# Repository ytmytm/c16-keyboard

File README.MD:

# C16 USB Keyboard

This project is designed to allow a modern USB keyboard to be used with a Commodore C16 or Commodore C64 instead of the original Commodore keyboard.

It is intended to be plugged into the internal 20-pin keyboard connector.

This project was forked from the [C128 USB Keyboard project](https://github.com/ytmytm/C128-keyboard),
which was based on [Hartland/C64-Keyboard](https://github.com/Hartland/C64-Keyboard).
The hardware and firmware have been adapted to the C16 keyboard matrix and MT8808 switch chip.

Only the USB interface is retained; PS/2 keyboards are becoming retro themselves.

This project requires a Seeed Studio XIAO SAMD21, which has a USB-C socket. Use a USB-A female to USB-C male OTG adapter to connect a standard PC keyboard.

-- Maciej 'YTM/Elysium' Witkowiak

<!---  -->

# Features

- supports USB HID boot-protocol keyboards, including compatible wireless USB receivers
- C16 positional and symbolic maps switchable on the fly
- OLED display support
- adapter can be plugged directly into keyboard port

# PCB and schematic

Use KiCad to open the project in [kicad-c128keyb](kicad-c128keyb/) folder.

In the [kicad-c128keyb/plots](kicad-c128keyb/plots) you will find ready to use Gerber files for manufacturing
as well as [schematic](kicad-c128keyb/plots/kicad-c128keyb.pdf)

Use the Gerber files from this repository when ordering the C16 PCB.

## Parts

* SEEED XIAO SAMD21 (important: SAMD21, not RP2040)
* U1: MT8808
* U2: 74HCT595
* C1, C2: 100n capacitors
* pin headers and sockets
* 128x32 SSD1306 I2C OLED display (optional)

C16 option:

* use J5 as keyboard connector
* J4 to provide power, connect +5V to the square pad
* don't install Q1 and R1

C64 option:

* use J2 as keyboard connector
* Q1: 2N3904 transistors (or any other NPN, like S9013)
* R1: 10K resistors

### C16 option

There is no +5V pin connected to keyboard connector in C16. Connect +5V from anywhere inside computer (e.g. one of the legs of C22 - yellow square on the photo below) to the square pad of J4.

### Restore key (C64 only)

Install Q1 and R1.

# Firmware

The sketch is in [SEEED/C16_keyboard](SEEED/C16_keyboard/). Keep all files in
that folder together when copying it to another computer.

## Install and upload with Arduino IDE

1. Install the **Seeed SAMD Boards** package and select the **Seeeduino XIAO**
   board (SAMD21). Follow the [Seeed setup instructions](https://wiki.seeedstudio.com/Seeeduino-XIAO/#software)
   to add the board package URL if necessary.
2. Use the Library Manager to install **[U8g2](https://github.com/olikraus/U8g2_Arduino)**
   and **[ShiftRegister74HC595](https://github.com/Simsso/ShiftRegister74HC595)**.
   U8g2 is required to compile the sketch even when no OLED is connected.
3. Download **`SEEED/C64_USB_Host_Library_SAMD.zip` from this repository**
   ([download the matching ZIP](SEEED/C64_USB_Host_Library_SAMD.zip)). In the IDE,
   choose **Sketch > Include Library > Add .ZIP Library** and select that local
   file. Alternatively, replace the installed library with this checkout's
   [source directory](SEEED/C64_USB_Host_Library_SAMD).
   A generic USB host library is not a substitute for this modified version.
4. Open [C16_keyboard.ino](SEEED/C16_keyboard/C16_keyboard.ino) in the Arduino IDE.
5. Disconnect the USB keyboard/OTG adapter and connect the XIAO's USB-C port
   to the computer with a USB data cable. Select the board's port and upload.
   If the port is missing or upload fails, enter the bootloader as described
   below, select its port, and try again.
6. Disconnect the programming cable, reconnect the keyboard through the OTG
   adapter, and power the adapter using the configuration described above.

Install the matching USB library on **the computer that compiles the sketch**.
Updating only the sketch or the Git checkout does not update an independently
installed library. The sketch rejects older library headers at compile time.

### Replacing the library on Windows

1. Close Arduino IDE and locate the sketchbook folder shown in its Preferences.
   Its library directory is usually `Documents\Arduino\libraries`, but the
   sketchbook may be elsewhere, including under OneDrive.
2. Move the old `C64_USB_Host_Library_SAMD` folder outside the `libraries`
   directory, then extract the current ZIP there. Replace the whole folder.
3. Check that the resulting layout is
   `libraries\C64_USB_Host_Library_SAMD\library.properties`, with no extra
   nested `C64_USB_Host_Library_SAMD` directory.
4. Restart the IDE and compile again. If multiple libraries are reported for
   `KeyboardController.h`, enable verbose compilation output and check the
   selected path. Remove or replace any outdated copy being selected.

On systems that support symbolic links, the installed library directory can
instead link to this checkout's `SEEED/C64_USB_Host_Library_SAMD` directory.
Move the old copy outside `libraries` and restart the IDE after changing it.

## Compile with the checkout's library using Arduino CLI

Run from the repository root. The Seeed SAMD board package, U8g2 and
ShiftRegister74HC595 must already be installed for Arduino CLI.

Bash (Linux/macOS):

```sh
arduino-cli compile \
  --fqbn Seeeduino:samd:seeed_XIAO_m0 \
  --library "$PWD/SEEED/C64_USB_Host_Library_SAMD" \
  SEEED/C16_keyboard
```

PowerShell (Windows):

```powershell
arduino-cli compile --fqbn Seeeduino:samd:seeed_XIAO_m0 --library ".\SEEED\C64_USB_Host_Library_SAMD" ".\SEEED\C16_keyboard"
```

The explicit [`--library` option](https://arduino.github.io/arduino-cli/1.5/sketch-build-process/#dependency-resolution)
has priority over libraries installed in the sketchbook. These commands use
the source directory directly, so no USB library ZIP installation is needed.
They compile the firmware; use the Arduino IDE or an appropriate CLI upload
command to upload it to the board.

The automated build pins Arduino CLI **1.5.1**, Seeed SAMD Boards **1.8.6**,
U8g2 **2.36.19** and ShiftRegister74HC595 **1.3.1**; see
[firmware.yml](.github/workflows/firmware.yml) for the build configuration.

## Entering the bootloader (double reset)

The original XIAO SAMD21 has reset pads rather than an onboard reset button.
To enter its bootloader:

1. Disconnect the keyboard/OTG adapter and connect the XIAO to the computer
   with a USB data cable.
2. Briefly bridge the two **RST reset pads twice in quick succession**, removing
   the bridge between the two touches. See [Seeed's reset-pad illustration](https://wiki.seeedstudio.com/Seeeduino-XIAO/#enter-bootloader-mode)
   for the pad locations. If your board has a reset button, press it twice.
3. The bootloader LED should pulse. With a UF2-enabled bootloader, a removable
   drive normally named **Arduino** appears, containing `INFO_UF2.TXT`.
   A bootloader serial port may also appear; on Windows its COM number may
   differ from the application port. Select that port for an IDE upload.

A single reset restarts the application. **Print Screen on the USB keyboard
only resets the adapter's keys and settings; it does not enter the bootloader.**

## Uploading a UF2 file by copying it to the boot drive

The [XIAO SAMD21 UF2 bootloader supports drag-and-drop flashing](https://wiki.seeedstudio.com/Seeeduino-XIAO-CircuitPython/#installing-circuitpython).
With a UF2-enabled bootloader and a UF2 build of **this project's firmware for
XIAO SAMD21**, no Arduino IDE is needed on the computer doing the upload:

1. Enter the bootloader using the double-reset procedure above.
2. Copy the firmware `.uf2` file to the **Arduino** removable drive using
   Windows File Explorer or your system's file manager.
3. Wait for copying to finish. The board normally restarts automatically and
   the boot drive disappears. Reconnect the keyboard/OTG adapter for use.

Prebuilt firmware is produced by the [Firmware build workflow](.github/workflows/firmware.yml)
and can be downloaded from a successful Actions run or a GitHub Release after
its build completes. The UF2 already contains the compiled libraries; its
recipient does not need Arduino IDE or the USB library ZIP.

Compiled binaries are not tracked in Git. The library ZIP is installed on the
build computer; it is not copied to the board's boot drive.
A `.bin` file cannot be used by simply renaming it to `.uf2`.

### Creating a UF2 from an Arduino build

1. Build for **Seeeduino XIAO (SAMD21)** with the matching USB library, then
   use **Sketch > Export Compiled Binary** in the Arduino IDE. Locate the
   application binary, normally named `C16_keyboard.ino.bin`.
2. Download [uf2conv.py](https://github.com/microsoft/uf2/blob/master/utils/uf2conv.py)
   and [uf2families.json](https://github.com/microsoft/uf2/blob/master/utils/uf2families.json)
   from Microsoft's UF2 project and place them alongside the binary.
3. In that directory, run the conversion with Python 3 (adjust the binary
   filename if your build uses a different one):

   ```sh
   python uf2conv.py --convert --family SAMD21 --base 0x2000 --output C16_keyboard.uf2 C16_keyboard.ino.bin
   ```

Use the application binary from this sketch's XIAO SAMD21 build, without a
bootloader image prepended. The `0x2000` application address matches the
[Seeed XIAO linker configuration](https://github.com/Seeed-Studio/ArduinoCore-samd/blob/master/variants/XIAO_m0/linker_scripts/gcc/flash_with_bootloader.ld).
The conversion only creates the UF2 file; copy it to the boot drive separately.

## OLED and firmware version

The optional display is a **128 × 32 SSD1306 I²C OLED at address `0x3C`**.
The firmware probes for it at startup and skips display operations if it does
not respond. The keyboard functions work without it.

The OLED shows the firmware release date below startup USB status messages,
for example `USB Configuring` / `FW 2026-10-31`. The version also appears below
`USB Running`. Status messages are cleared after about five seconds of
inactivity; key events replace them with the key display.

Set the release date in [firmware_version.h](SEEED/C16_keyboard/firmware_version.h)
when preparing a new firmware release. Recompiling the same source does not
change its version.

## Keyboard compatibility

The USB driver uses HID boot-protocol reports with six ordinary key slots and
separate modifier bits. A keyboard that only supports a proprietary or
NKRO-only report format may not work. Wireless keyboards need a compatible
USB receiver; Bluetooth-only keyboards cannot connect directly.

The adapter reads raw USB HID usages, so the PC's operating-system keyboard
layout does not configure it. The symbolic maps assume US-style key labels.
For troubleshooting, Right Shift should appear as HID usage `0xE5` with
modifier mask `0x20`. `getOemKey()` returns the HID usage; `getKey()` returns
ASCII and is not used to map the Commodore keyboard matrix.

The companion C64 sketch is [SEEED/C64_keyboard/C64_keyboard.ino](SEEED/C64_keyboard/C64_keyboard.ino).
It uses the same modified USB library. Select that folder instead of
`SEEED/C16_keyboard` when building for C64. The C16 firmware has only its
C16 positional and symbolic layouts and no joystick emulation.

## Tests and automated builds

Run the following commands from the repository root with Python 3 and g++ installed:

```sh
python3 tests/test_keyboard_events.py
python3 tests/test_keyboard_events.py C64
python3 -m unittest discover -s tests -p 'test_firmware_artifacts.py' -v
```

The tests exercise the real HID parser and firmware callbacks with mocked
hardware, including simultaneous modifiers, both Shifts, Shift Lock,
differential Shift, shared switches, saved releases, reset and USB reconnect.
See [tests/README.md](tests/README.md).

GitHub Actions runs these tests, compiles both sketches and packages verified
C16 `.bin`, `.elf` and `.uf2` files, build metadata and SHA-256 checksums.
A published release also receives those files. Before publishing, update
`SEEED/C16_keyboard/firmware_version.h`, run the tests and build, commit the
changes and tag that commit `vYYYY-MM-DD` to match the firmware date. Push the
commit and tag, then publish a GitHub Release for that tag to trigger attachment
of the verified firmware files. A tag push alone does not attach release files.
If changing the USB library, rebuild its installation ZIP with
`python3 tools/package_usb_library.py` and commit the updated ZIP too.

# Keyboard mapping

Key maps are defined in [SEEED/C16_keyboard/keymaps.h](SEEED/C16_keyboard/keymaps.h) and [SEEED/C64_keyboard/keymaps.h](SEEED/C64_keyboard/keymaps.h).

You can modify existing ones or add your own.

If you add a new keymap you need to add it to `keymaps[]` array at the bottom of that file. The first key map in that array is the default one.

Press **Pause** to cycle between the two layouts for the selected sketch.
Startup and **Print Screen** reset select the positional layout.
**Scroll Lock** toggles Shift Lock. These settings are not saved across power cycles.

Both physical Shifts, Shift Lock and differential mappings share the C16 Shift
switch. Releases use the mapping saved on key-down, even after a layout change.
Unplugging the USB keyboard clears held keys and Shift Lock.
In the C16 sketch, **Print Screen** clears ordinary held keys and Shift Lock,
selects the positional layout, and restores still-held USB modifiers using that
layout. Release and press an ordinary key again to reactivate it after reset.

The C16 event state uses a fixed table for six ordinary keys and eight modifiers.
The sketch stores its keyboard object statically and prints OLED text directly,
without `std::map`, `new` or Arduino `String` allocations in its own event and
display code.

## C16 positional (default for C16)

This is a mixture of C16/Plus4/C64 and Vice layout.

| USB key | C16 key |
|---------|----------|
| ESC | RUN/STOP |
| F1 | F1 |
| F2 | F4 (shift+F1) |
| F3 | F2 |
| F4 | F5 (shift+F2) |
| F5 | F3 |
| F6 | F6 (shift+F3) |
| F7 | HELP |
| F8 | F7 (shift+HELP) |
| ` ~ | ESC |
| - | + |
| + | - |
| [ | @ |
| ] | * |
| \ | = |
| ; | : |
| ' " | ; |
| Tab | CTRL |
| Caps lock | RUN/STOP |
| Home | CLR/HOME |
| End | RUN/STOP |
| Delete | DEL |
| Backspace | DEL |
| Insert | POUND |
| Page down | Shift+= (left arrow); ignored with Shift |
| Page up | Shift+0 (up arrow); ignored with Shift |
| left CTRL | C= key |
| left/right SHIFT | SHIFT |
| left Windows | ignored |
| right Alt | POUND |
| right Windows | POUND |
| right CTRL | = |
| Print Screen | reset MT8808 switchboard |
| Scroll Lock | Shift Lock |
| Pause | switch to next keymap |
| (keypad) | digits 1-9,0 |
| (cursors) | cursors |

## C16 symbolic

Both physical Shifts map to C16 SHIFT; both Windows keys map to C=.
Right Alt is ignored.

| USB key | C16 key |
|---------|----------|
| ESC | ESC |
| F1 | F1 |
| F2 | F4 (shift+F1) |
| F3 | F2 |
| F4 | F5 (shift+F2) |
| F5 | F3 |
| F6 | F6 (shift+F3) |
| F7 | HELP |
| F8 | F7 (shift+HELP) |
| ` ~ | (left arrow) |
| \ | POUND |
| Tab | CTRL |
| Caps lock | RUN/STOP |
| Home | CLR/HOME |
| End | RUN/STOP |
| Delete | DEL |
| Backspace | DEL |
| left CTRL | CTRL |
| right CTRL | CTRL |
| left Windows | C= key |
| Print Screen | reset MT8808 switchboard |
| Scroll Lock | Shift Lock |
| Pause | switch to next keymap |
| (keypad) | digits 1-9,0 |
| (cursors) | cursors |

As you would expect from standard keycaps, e.g. SHIFT+2 is '@', not '"'.

## C64 positional (default for C64)

This layout works best if you have muscle memory of the original keyboard.

| USB key | C64 key |
|---------|----------|
| ESC | RUN/STOP |
| F1 | F1 |
| F2 | F2 (Shift+F1) |
| F3 | F3 |
| F4 | F4 (Shift+F3) |
| F5 | F5 |
| F6 | F6 (Shift+F5) |
| F7 | F7 |
| F8 | F8 (Shift+F7) |
| F9–F12 | ignored |
| Print Screen | reset MT8808 switchboard |
| Scroll Lock | Shift Lock |
| Pause | switch to next keymap |
| Insert | POUND |
| Home | CLR/HOME |
| Page Up | RESTORE |
| End | RUN/STOP |
| (keypad) | digits 1-9,0 |
| left CTRL | C= key |
| left SHIFT | left SHIFT |
| right SHIFT | right SHIFT |
| AltGr | RESTORE |

## C64 symbolic

As you would expect from standard keycaps, e.g. SHIFT+2 is '@', not '"'.

It uses the same F1–F8 mappings and adapter controls as the C64 positional map.
Other changes:

- Insert maps to INST (Shift+DEL); Delete maps to DEL
- both left and right CTRL mapped to CTRL
- both left and right Windows mapped to C= key
- AltGr is RESTORE

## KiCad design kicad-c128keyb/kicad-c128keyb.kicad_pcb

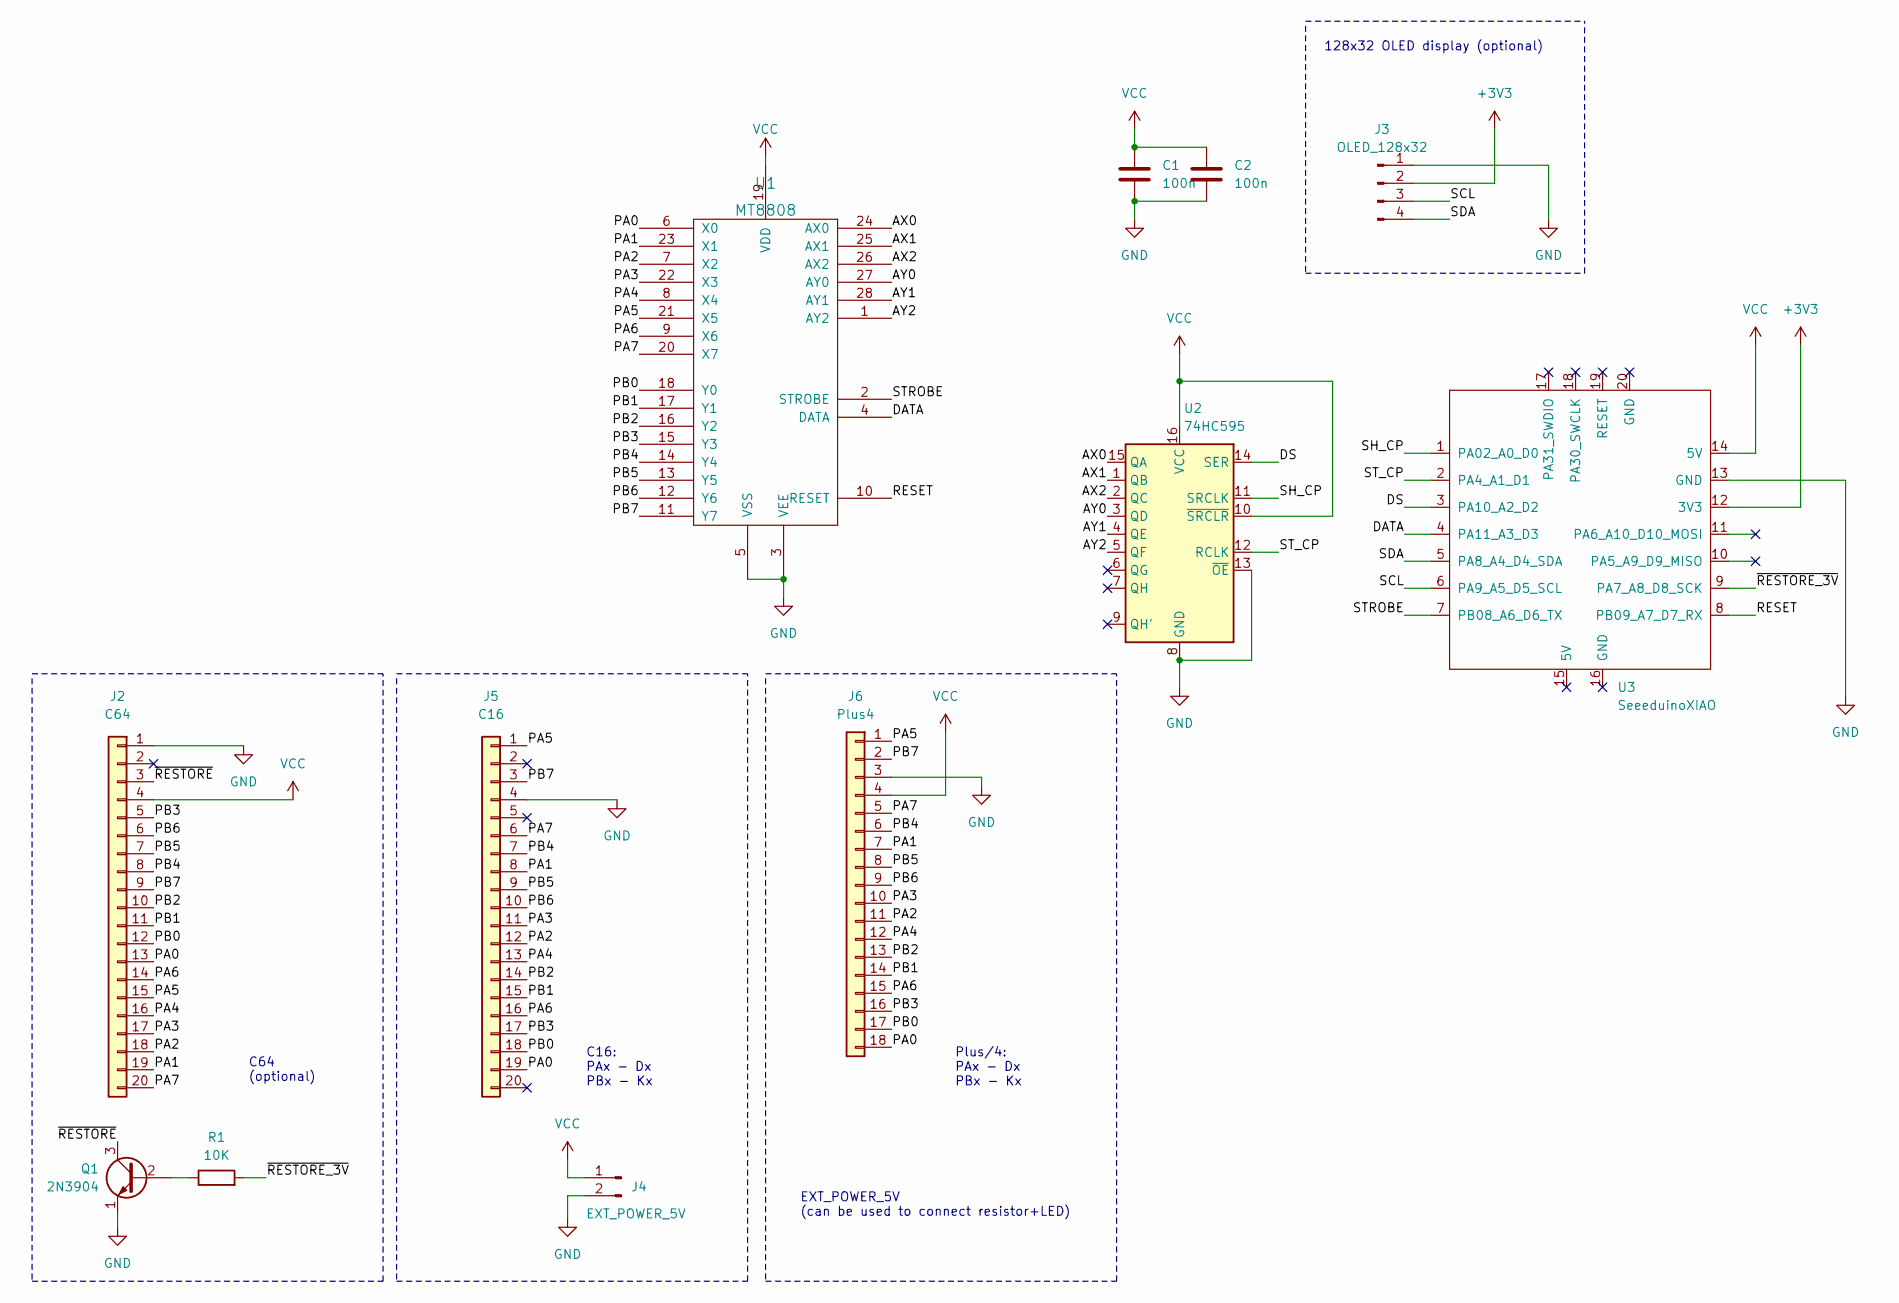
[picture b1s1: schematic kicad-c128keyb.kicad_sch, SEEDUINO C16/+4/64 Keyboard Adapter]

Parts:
C1, C2: 100n; C_Disc_D4.3mm_W1.9mm_P5.00mm
J2: C64; PinHeader_1x20_P2.54mm_Vertical
J3: OLED_128x32; PinHeader_1x04_P2.54mm_Vertical
J4: EXT_POWER_5V; PinHeader_1x02_P2.54mm_Vertical
J5: C16; PinHeader_1x20_P2.54mm_Vertical
J6: Plus4; PLUS4_KEYBOARD
Q1: 2N3904; TO-92_Inline
R1: 10K; R_Axial_DIN0207_L6.3mm_D2.5mm_P7.62mm_Horizontal
U1: MT8808; DIP-28_W15.24mm_Socket
U2: 74HC595; DIP-16_W7.62mm_Socket
U3: SeeeduinoXIAO; XIAO-Generic-Hybrid-14P-2.54-21X17.8MM

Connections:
+3V3: J3.2, U3.12 (3V3)
/AX0: U1.24 (AX0), U2.15 (QA)
/AX1: U1.25 (AX1), U2.1 (QB)
/AX2: U1.26 (AX2), U2.2 (QC)
/AY0: U1.27 (AY0), U2.3 (QD)
/AY1: U1.28 (AY1), U2.4 (QE)
/AY2: U1.1 (AY2), U2.5 (QF)
/DATA: U1.4 (DATA), U3.4 (PA11_A3_D3)
/DS: U2.14 (SER), U3.3 (PA10_A2_D2)
/PA0: J2.13, J5.19, J6.18, U1.6 (X0)
/PA1: J2.19, J5.8, J6.7, U1.23 (X1)
/PA2: J2.18, J5.12, J6.11, U1.7 (X2)
/PA3: J2.17, J5.11, J6.10, U1.22 (X3)
/PA4: J2.16, J5.13, J6.12, U1.8 (X4)
/PA5: J2.15, J5.1, J6.1, U1.21 (X5)
/PA6: J2.14, J5.16, J6.15, U1.9 (X6)
/PA7: J2.20, J5.6, J6.5, U1.20 (X7)
/PB0: J2.12, J5.18, J6.17, U1.18 (Y0)
/PB1: J2.11, J5.15, J6.14, U1.17 (Y1)
/PB2: J2.10, J5.14, J6.13, U1.16 (Y2)
/PB3: J2.5, J5.17, J6.16, U1.15 (Y3)
/PB4: J2.8, J5.7, J6.6, U1.14 (Y4)
/PB5: J2.7, J5.9, J6.8, U1.13 (Y5)
/PB6: J2.6, J5.10, J6.9, U1.12 (Y6)
/PB7: J2.9, J5.3, J6.2, U1.11 (Y7)
/RESET: U1.10 (RESET), U3.8 (PB09_A7_D7_RX)
/SCL: J3.3, U3.6 (PA9_A5_D5_SCL)
/SDA: J3.4, U3.5 (PA8_A4_D4_SDA)
/SH_CP: U2.11 (SRCLK), U3.1 (PA02_A0_D0)
/STROBE: U1.2 (STROBE), U3.7 (PB08_A6_D6_TX)
/ST_CP: U2.12 (RCLK), U3.2 (PA4_A1_D1)
/~RESTORE_3V: R1.2, U3.9 (PA7_A8_D8_SCK)
/~RESTORE: J2.3, Q1.3 (C)
GND: C1.2, C2.2, J2.1, J3.1, J4.2, J5.4, J6.3, Q1.1 (E), U1.3 (VEE), U1.5 (VSS), U2.8 (GND), U2.13 (~OE), U3.13 (GND)
unnamed: Q1.2 (B), R1.1
VCC: C1.1, C2.1, J2.4, J4.1, J6.4, U1.19 (VDD), U2.10 (~SRCLR), U2.16 (VCC), U3.14 (5V)

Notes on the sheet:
C16: PAx - Dx PBx - Kx
C64 (optional)
128x32 OLED display (optional)
EXT_POWER_5V (can be used to connect resistor+LED)
Plus/4: PAx - Dx PBx - Kx

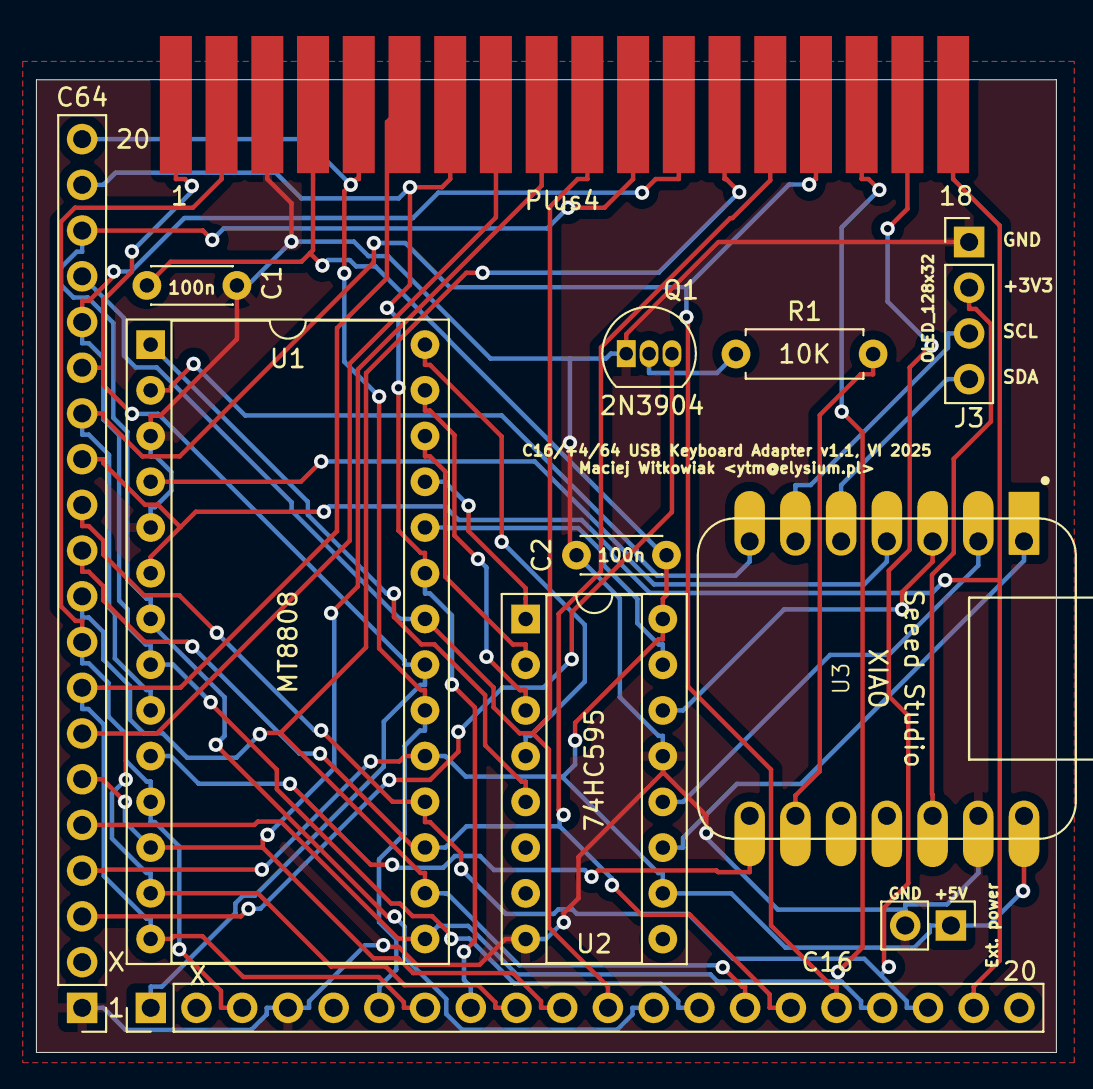
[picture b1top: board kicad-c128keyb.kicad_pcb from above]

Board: 2 copper layers, 56.7 x 54.0 mm, 12 parts (0 on the bottom side), 36 nets.

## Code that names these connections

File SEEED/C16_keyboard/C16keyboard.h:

/*
  C16keyboard - Commodore Keyboard library

  Copyright (c) 2022 Hartland PC LLC
  Written by Robert VanHazinga

  Modified for C16 by Maciej 'YTM/Elysium' Witkowiak


    This program is free software: you can redistribute it and/or modify
    it under the terms of the GNU General Public License as published by
    the Free Software Foundation, either version 3 of the License, or
    (at your option) any later version.

    This program is distributed in the hope that it will be useful,
    but WITHOUT ANY WARRANTY; without even the implied warranty of
    MERCHANTABILITY or FITNESS FOR A PARTICULAR PURPOSE.  See the
    GNU General Public License for more details.

    You should have received a copy of the GNU General Public License
    along with this program.  If not, see <https://www.gnu.org/licenses/>.

*/


#ifndef C16keyboard_h
#define C16keyboard_h

#include <array>

#if defined(ARDUINO) && ARDUINO >= 100
#include "Arduino.h"
#else
#include "WProgram.h"
#endif

//MT88xx control pins
#define ANALOG_SW_DATA      3 // Sets selected cross switch on/off
#define ANALOG_SW_STROBE    6 // Strobe timing pulse
#define ANALOG_SW_RESET     7 // Reset all MT88XX cross switches to off

// I2C DISPLAY
#define SDA_PIN             4 // just for reference, native SEEDUINO XIAO doesn't need these defines
#define SCL_PIN             5

// 74HC595 shift register pins
#define SH_CP_PIN           0 // SRCLK // 11th pin // clock
#define ST_CP_PIN           1 // RCLK  // 12th pin // latch
#define DS_PIN              2 // SER   // 14th pin // data

// Six address bits from the shift register to the MT8808 (8 by 8).
#define ANALOG_SH_AX0     0 // QA (15)
#define ANALOG_SH_AX1     1 // QB (1)
#define ANALOG_SH_AX2     2 // ...
#define ANALOG_SH_AY0     3
#define ANALOG_SH_AY1     4
#define ANALOG_SH_AY2     5
const uint8_t ANALOG_SH_ARRAY[] = { ANALOG_SH_AY2, ANALOG_SH_AY1, ANALOG_SH_AY0, ANALOG_SH_AX2, ANALOG_SH_AX1, ANALOG_SH_AX0 };
// Shift-register outputs QG and QH are unused.

// C16 matrix addresses and adapter actions.
#include "keymapping.h"

class C16KeyInfo {
  public:
    constexpr C16KeyInfo(const uint16_t c, const char* name) :
    m_keycode(c), m_name(name)
    {};
    constexpr auto get_keycode() const { return m_keycode; }
    constexpr const char* get_name() const { return m_name; };
  private:
    const uint16_t m_keycode;
    const char *m_name;
};

// HID boot reports hold at most six ordinary keys and eight modifiers.
struct HeldKey {
    uint8_t usage = 0;
    uint16_t mapped = IGNORE_KEYCODE;
};

class C16keyboard {
  public:
    void begin(void);
    void setKey(uint16_t c, bool kpress, uint8_t kc);
    uint16_t mapkeycode(uint8_t kc);
    void clearAllKeys(void);
    void updateShiftSwitches(void);
    void restoreModifiers(uint8_t modifiers);
    constexpr uint8_t getNumKeyMaps(void);
    const char* getCurrentKeyMapName(void);
};

class C16Key {
  public:
    constexpr C16Key(const int16_t keycode, const uint16_t unshifted, const uint16_t shifted) :
    m_keycode(keycode), m_unshifted(unshifted), m_shifted(shifted)
    {};
    constexpr auto get_keycode() const { return m_keycode; }
    constexpr uint16_t get(bool shifted = false) const {
      return shifted ? m_shifted : m_unshifted;
    }
  private:
    const int16_t m_keycode;
    const uint16_t m_unshifted, m_shifted;
};

using ModifierMap = std::array<uint16_t, 8>;

class C16KeyMap {
  public:
    constexpr C16KeyMap(const char* name, const C16Key *map, const uint16_t mapsize, const ModifierMap &mods) :
    m_name(name), m_map(map), m_mapsize(mapsize), m_mods(mods)
    {};
    constexpr const char* getName() const { return m_name; };
    constexpr const ModifierMap &getMods() const { return m_mods; };
    constexpr C16Key getKey(uint8_t keycode) const {
      for (uint16_t i = 0; i < m_mapsize; ++i) {
        if (m_map[i].get_keycode() == keycode) {
          return m_map[i];
        }
      }
      return C16Key(0, IGNORE_KEYCODE, IGNORE_KEYCODE);
    }
  private:
    const char *m_name;
    const C16Key *m_map;
    const uint16_t m_mapsize;
    const ModifierMap &m_mods;
};

#endif

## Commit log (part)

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2024-10-09 common C16/C64 version for internal mount; despite filenames this is not about C128 anymore; downgraded from MT8816 to MT8808
2024-10-15 move folder to C16
2024-10-15 move files to C16
2024-10-15 docs
2024-10-15 C128->C16 renames
2024-10-16 remove all C128-related, joystick and MT8812/16 stuff
2024-10-16 C16 symbolic keymap and list of key definitions
2024-10-16 correct slash/dot/comma confusion
2024-10-16 reference for key layout definitions
2024-10-16 new PCB render
2024-10-16 drop C128-related files
2024-10-16 C64 firmware
2024-10-16 updated for C16/64 combination
2024-10-22 fix for missed key release events (e.g. in symbolic mapping after shift+' for double-quote, shift had to be released last)
2024-10-22 don't use u8g2 if the display is not connecte (i2c address 0x3c)
2024-10-24 C16 positional keymap
2024-10-24 don't use u8g2 if the display is not connected (i2c address 0x3c)
2024-10-24 drop unneeded file
2026-06-14 added connector for Plus/4 ribbon cable; bumped to KiCad 9
